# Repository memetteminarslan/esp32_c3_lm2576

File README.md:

### ESP32_C3_LM2576
The ESP32 C3 module board is a design with an LM2576 integrated circuit that converts a wide input voltage range of 12V to 36V into 5V. It serves as a platform hosting the ESP32 C3 microcontroller, offering low power consumption and advanced wireless connectivity capabilities such as WiFi and Bluetooth Low Energy (BLE).

The ESP32 C3 is a microcontroller with a 32-bit RISC-V core capable of processing at an advanced speed while maintaining low power consumption. It can easily connect to wireless networks through WiFi and efficiently operate in low-power applications with its Bluetooth LE support.

The LM2576 integrated circuit is a buck (step-down) power converter that operates with high efficiency. It converts the wide input voltage range to a fixed 5V output voltage to meet the power requirements of the ESP32 C3 module. This design is an ideal solution for applications with high input voltages, as it can efficiently handle them.

The ESP32 C3 module board is an impressive IoT (Internet of Things) platform that combines low power consumption with high performance. It can be used in various applications such as industrial automation, smart home systems, wireless sensor networks, and many others. Moreover, thanks to its wide input voltage range, it can be powered by different power sources, providing a flexible and reliable solution.

This module board combines the powerful capabilities of the ESP32 C3 and the efficiency of the LM2576 power converter, making it an excellent foundational platform for various electronic projects.

If you have any questions, contact : memetteminarslan@gmail.com

Schematic

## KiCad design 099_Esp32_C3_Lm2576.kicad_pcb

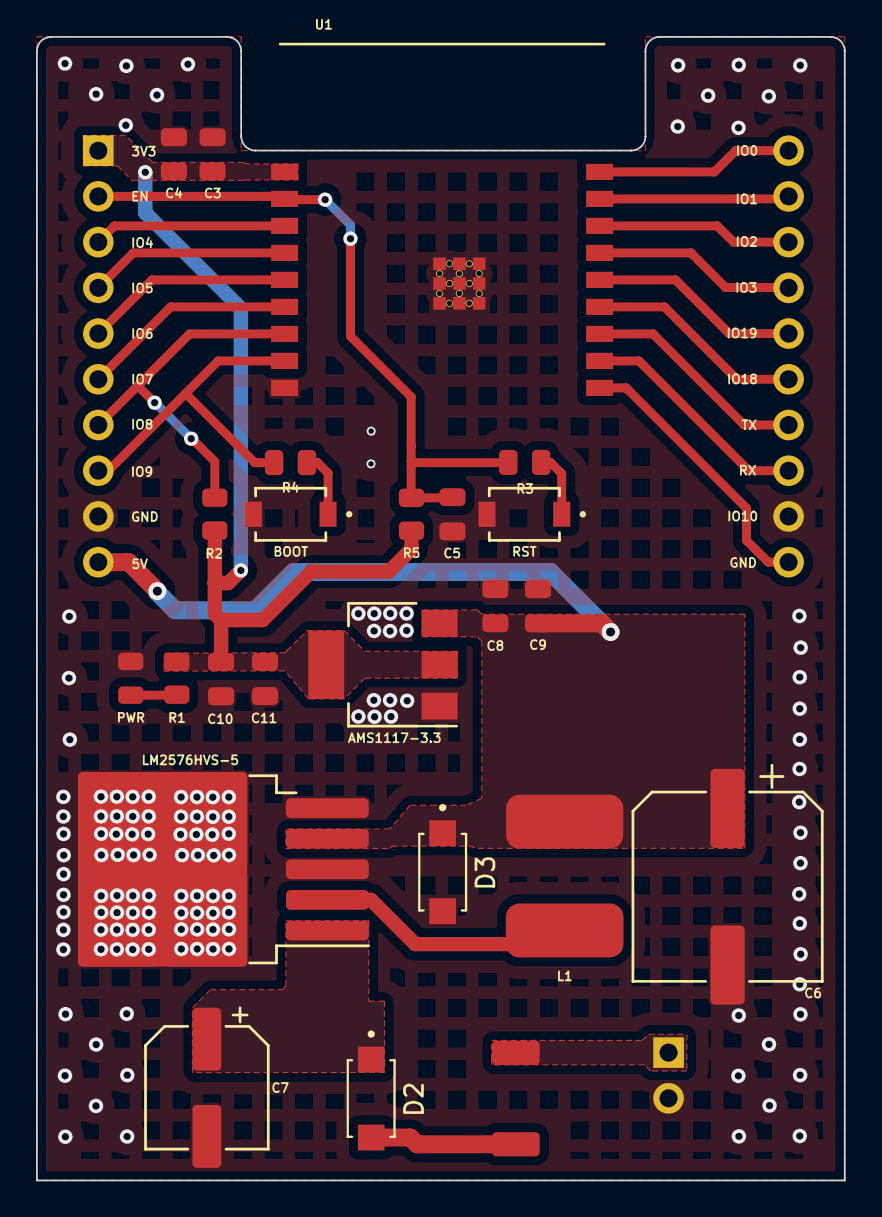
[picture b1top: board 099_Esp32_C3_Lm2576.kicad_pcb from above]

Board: 2 copper layers, 44.9 x 63.5 mm, 27 parts (0 on the bottom side), 26 nets.

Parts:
BOOT: SW_Push; SW_TL1015AF160QG
C3, C4, C5, C8, C9, C10, C11: C; C_0805_2012Metric
C6: C_Polarized_Small; CP_Elec_10x12.6
C7: C_Polarized_Small; CP_Elec_6.3x7.7
D2, D3: SS310; SODFL5226X100N
F1: Fuse; Fuse_2010_5025Metric
J3: Screw_Terminal_01x02; PinHeader_1x02_P2.54mm_Vertical
J4, J5: Conn_01x10_Male; PinHeader_1x10_P2.54mm_Vertical
L1: L; 100uH
PWR: LED; LED_0805_2012Metric
R1, R2, R3, R4, R5: R; R_0805_2012Metric
RST: SW_Push; SW_TL1015AF160QG
U1: ESP32-C3-WROOM-02-N4; MODULE_ESP32-C3-WROOM-02-H4
U2: LM2576HVS-5; TO-263-5_TabPin3
U3: AMS1117-3.3; SOT-223-3_TabPin2

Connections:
+3V3: C3.1, C4.1, C10.1, C11.1, J4.1, R1.1, R2.1, R5.1, U1.1 (3V3), U3.2 (VO)
+5V: C6.1, C8.1, C9.1, D3.1, J4.10, L1.2, U2.4 (FB), U3.3 (VI)
+12V: F1.1, J3.1
EN: C5.1, J4.2, R3.1, R5.2, U1.2 (EN)
GND: BOOT.2, C3.2, C4.2, C5.2, C6.2, C7.2, C8.2, C9.2, C10.2, C11.2, D3.2, J3.2, J4.9, J5.9, PWR.1 (K), RST.2, U1.9 (GND), U1.19 (GND), U1.20 (GND), U1.21 (GND), U1.22 (GND), U1.23 (GND), U1.24 (GND), U1.25 (GND), U1.26 (GND), U1.27 (GND), U1.28 (GND), U1.29 (GND), U1.30 (GND), U1.31 (GND), U1.32 (GND), U1.33 (GND), U1.34 (GND), U1.35 (GND), U1.36 (GND), U1.37 (GND), U1.38 (GND), U2.3 (GND), U2.5 (~ON/OFF), U3.1 (GND)
IO0: J5.1, U1.18 (IO0)
IO1: J5.2, U1.17 (IO1)
IO2: J5.3, U1.16 (IO2)
IO3: J5.4, U1.15 (IO3)
IO4: J4.3, U1.3 (IO4)
IO5: J4.4, U1.4 (IO5)
IO6: J4.5, U1.5 (IO6)
IO7: J4.6, U1.6 (IO7)
IO8: J4.7, R2.2, U1.7 (IO8)
IO9: J4.8, R4.1, U1.8 (IO9)
IO10: J5.10, U1.10 (IO10)
IO18: J5.6, U1.13 (IO18)
IO19: J5.5, U1.14 (IO19)
unnamed: PWR.2 (A), R1.2
unnamed: D2.2, F1.2
unnamed: R3.2, RST.1
unnamed: BOOT.1, R4.2
unnamed: L1.1, U2.2 (OUT)
unnamed: C7.1, D2.1, U2.1 (VIN)
RX: J5.8, U1.11 (RXD)
TX: J5.7, U1.12 (TXD)
